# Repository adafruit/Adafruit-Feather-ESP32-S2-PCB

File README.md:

## Adafruit ESP32-S2 Feather

<a href="http://www.adafruit.com/products/5000"><br/>
Click here to purchase one from the Adafruit shop</a>

### ESP32-S2 Feather with BME280

<a href="http://www.adafruit.com/products/5303"><br/>
Click here to purchase one from the Adafruit shop</a>

PCB files for the Adafruit ESP32-S2 Feather 

Format is EagleCAD schematic and board layout
* https://www.adafruit.com/product/5000
* https://www.adafruit.com/product/5303

### Description

What's Feather-shaped and has an ESP32-S2 WiFi module? What has a STEMMA QT connector for I2C devices? What has your favorite Espressif WiFi microcontroller and lots of Flash and RAM memory for your next IoT project? What will make your next IoT project flyyyyy?

That's right - it's the new Adafruit ESP32-S2 Feather! With native USB and 4 MB flash + 2 MB of PSRAM, this board is perfect for use with CircuitPython or Arduino with low-cost WiFi. Native USB means it can act like a keyboard or a disk drive. WiFi means its awesome for IoT projects. And Feather means it works with the large community of Feather Wings for expandability.

The ESP32-S2 is a highly-integrated, low-power, 2.4 GHz Wi-Fi System-on-Chip (SoC) solution that now has built-in native USB as well as some other interesting new technologies like Time of Flight distance measurements. With its state-of-the-art power and RF performance, this SoC is an ideal choice for a wide variety of application scenarios relating to the Internet of Things (IoT), wearable electronics, and smart homes.

### License

Adafruit invests time and resources providing this open source design, please support Adafruit and open-source hardware by purchasing products from [Adafruit](https://www.adafruit.com)!

Designed by Limor Fried/Ladyada for Adafruit Industries.

Creative Commons Attribution/Share-Alike, all text above must be included in any redistribution. 
See license.txt for additional details.

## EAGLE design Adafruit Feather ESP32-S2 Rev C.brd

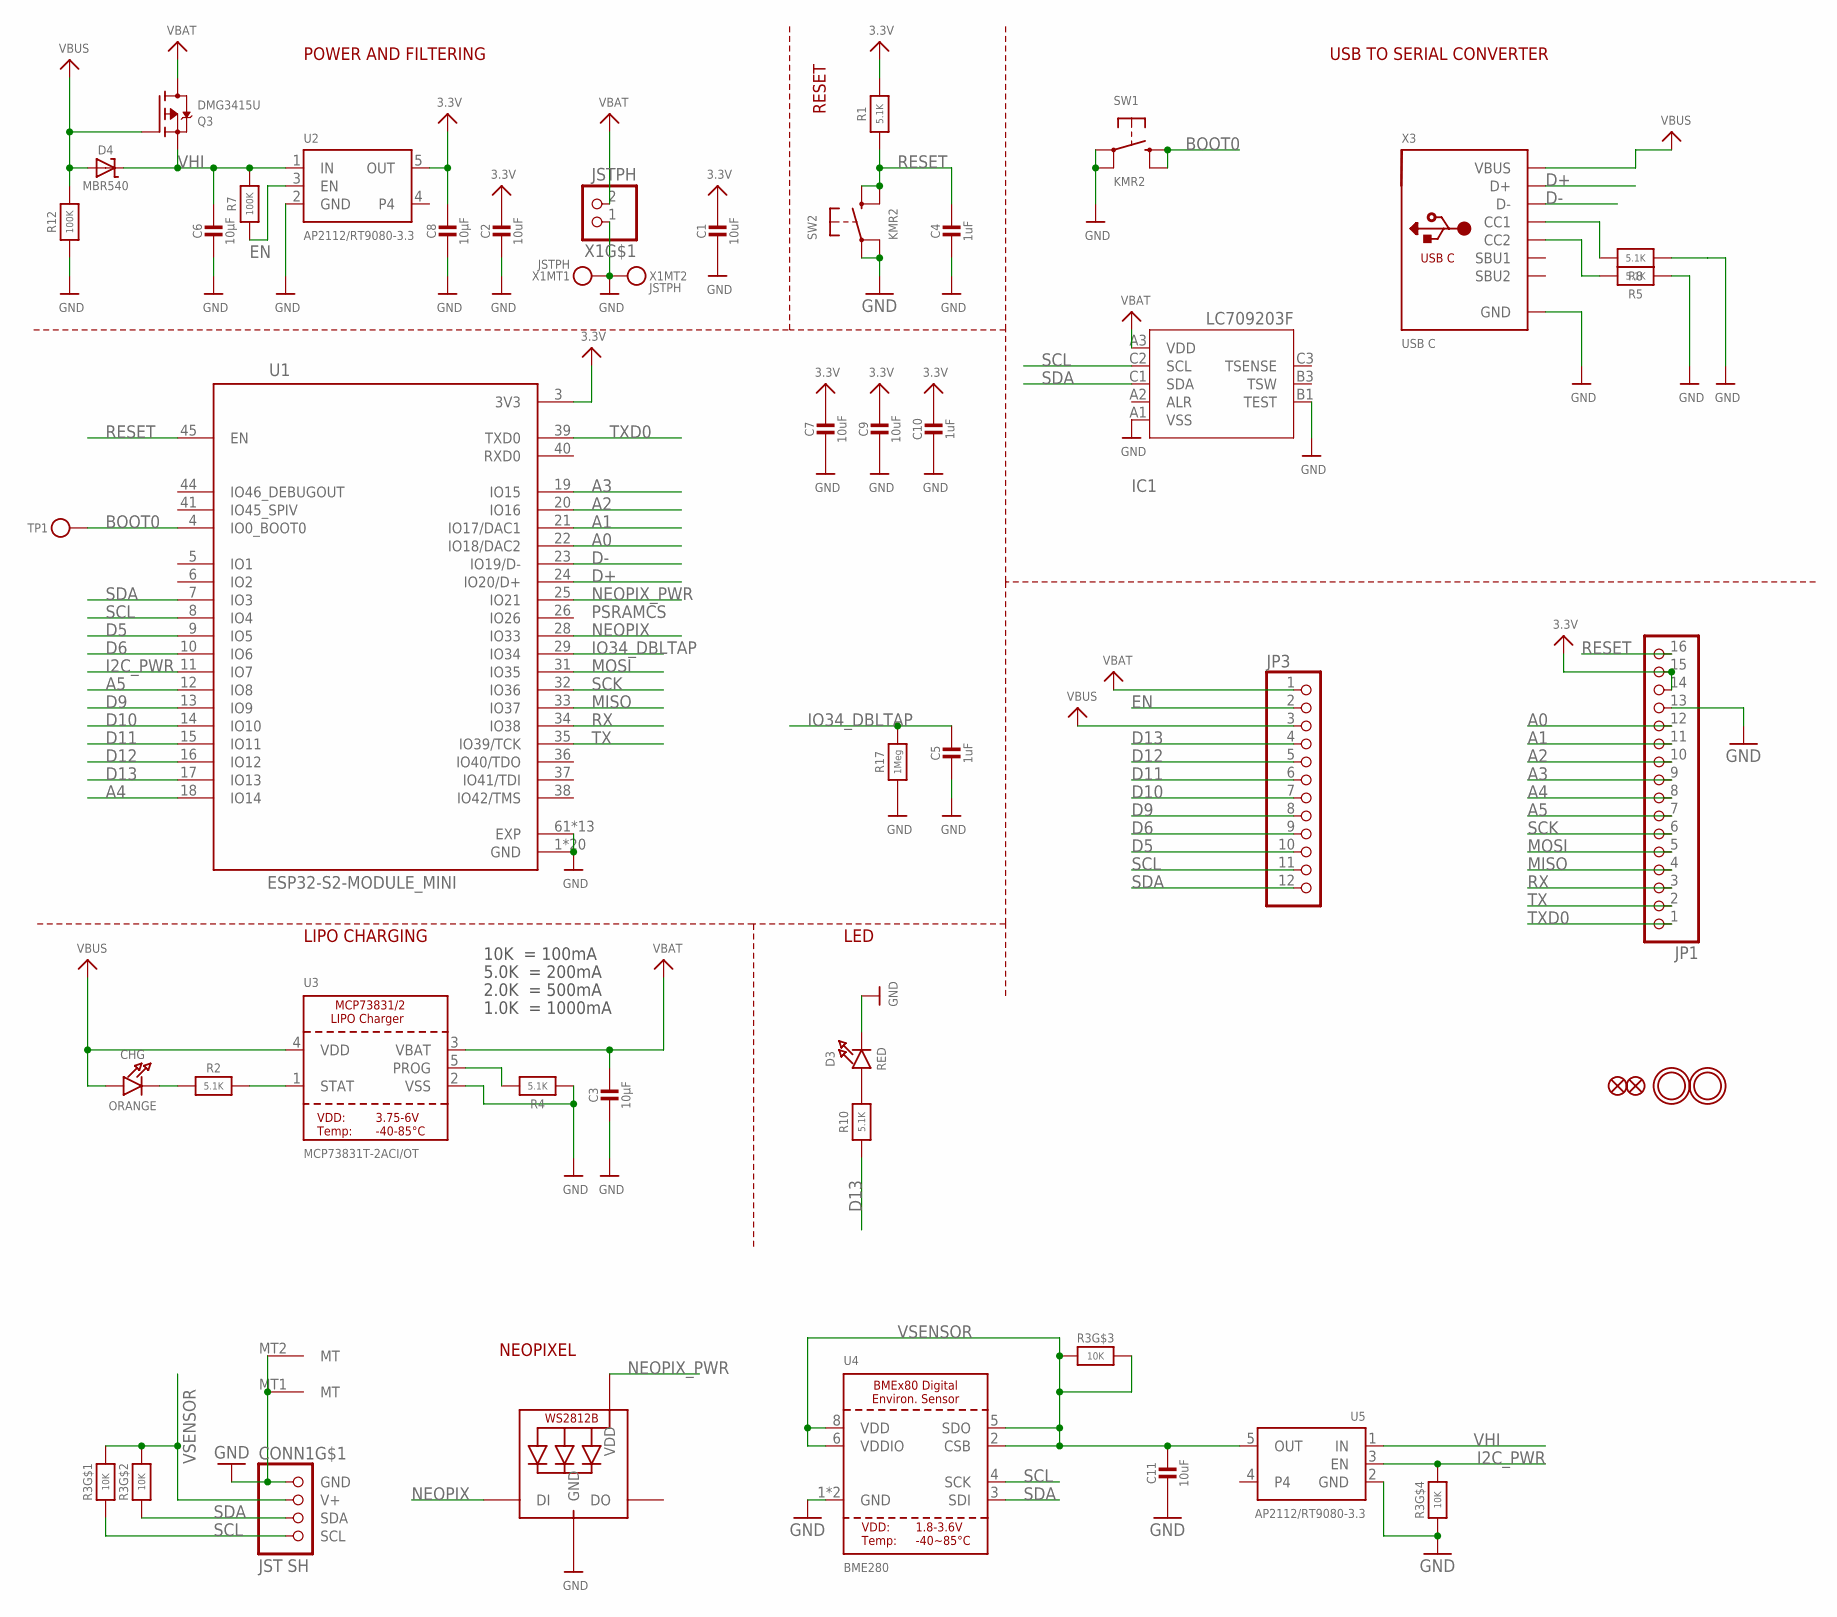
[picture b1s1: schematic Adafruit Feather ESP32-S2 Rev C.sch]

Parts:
C1, C2, C7, C9: 10uF; 0805-NO
C3, C6, C8: 10µF; 0805-NO
C4, C5, C10: 1uF; 0603-NO
C11: 10uF; _0805MP
CHG: ORANGE; CHIPLED_0603_NOOUTLINE
CONN1: JST SH; JST_SH4_RA
D3: RED; CHIPLED_0603_NOOUTLINE
D4: MBR540; SOD-123
IC1: LC709203F/MH; WLCSP9
JP1: HEADER-1X16ROUND; 1X16_ROUND
JP3: HEADER-1X12; 1X12_ROUND
LED1: WS2812B_SK6805_1515; SK6805_1515
Q3: DMG3415U; SOT23-R
R1, R2, R4, R5, R8, R10: 5.1K; 0603-NO
R3: 10K; RESPACK_4X0603
R7, R12: 100K; 0603-NO
R17: 1Meg; 0603-NO
SW1, SW2: KMR2; BTN_KMR2_4.6X2.8
TP1: TESTPOINTROUND1.5MMNO; TESTPOINT_ROUND_1.5MM_NO
U1: ESP32-S2-MODULE_MINI; QFN60_ESP32-S2-MINI-1_EXP
U2, U5: AP2112/RT9080-3.3; SOT23-5
U3: MCP73831T-2ACI/OT; SOT23-5
U4: BME280
U$31, U$32: MOUNTINGHOLE2.5; MOUNTINGHOLE_2.5_PLATED
U$34, U$35: FIDUCIAL_1MM
X1: JSTPH; JSTPH2_BATT
X3: USB C; USB_C_CUSB31-CFM2AX-01-X

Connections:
3.3V: C1.1, C2.1, C7.1, C8.1, C9.1, C10.1, JP1.14, JP1.15, R1.2, U1.3 (3V3), U2.5 (OUT)
A0: JP1.12, U1.22 (IO18/DAC2)
A1: JP1.11, U1.21 (IO17/DAC1)
A2: JP1.10, U1.20 (IO16)
A3: JP1.9, U1.19 (IO15)
A4: JP1.8, U1.18 (IO14)
A5: JP1.7, U1.12 (IO8)
BOOT0: SW1.B (S), SW1.B' (S1), TP1.P$1, U1.4 (IO0_BOOT0)
D5: JP3.10, U1.9 (IO5)
D6: JP3.9, U1.10 (IO6)
D9: JP3.8, U1.13 (IO9)
D10: JP3.7, U1.14 (IO10)
D11: JP3.6, U1.15 (IO11)
D12: JP3.5, U1.16 (IO12)
D13: JP3.4, R10.1, U1.17 (IO13)
D+: U1.24 (IO20/D+), X3.A6 (D+), X3.B6 (D+)
D-: U1.23 (IO19/D-), X3.A7 (D-), X3.B7 (D-)
EN: JP3.2, R7.1, U2.3 (EN)
GND: C1.2, C2.2, C3.2, C4.2, C5.2, C6.2, C7.2, C8.2, C9.2, C10.2, C11.2, CONN1.1 (GND), CONN1.MT1 (MT), CONN1.MT2 (MT), D3.C, IC1.A1 (VSS), IC1.B1 (TEST), JP1.13, LED1.4 (GND), R3.4 (1), R4.1, R5.1, R8.1, R12.1, R17.1, SW1.A, SW1.A' (P1), SW2.A, SW2.A' (P1), U1.1 (GND), U1.2 (GND), U1.30 (GND), U1.42 (GND), U1.43 (GND), U1.46 (GND), U1.47 (GND), U1.48 (GND), U1.49 (GND), U1.50 (GND), U1.51 (GND), U1.52 (GND), U1.53 (GND), U1.54 (GND), U1.55 (GND), U1.56 (GND), U1.57 (GND), U1.58 (GND), U1.59 (GND), U1.60 (GND), U1.61 (EXP), U1.62 (EXP), U1.63 (EXP), U1.64 (EXP), U1.65 (EXP), U1.66 (EXP), U1.67 (EXP), U1.68 (EXP), U1.69 (EXP), U1.70 (EXP), U1.71 (EXP), U1.72 (EXP), U1.73 (EXP), U2.2 (GND), U3.2 (VSS), U4.1 (GND), U4.7 (GND), U5.2 (GND), X1.1, X1.NC1, X1.NC2, X3.A1B12 (GND), X3.B1A12 (GND)
I2C_PWR: R3.5 (2), U1.11 (IO7), U5.3 (EN)
IO34_DBLTAP: C5.1, R17.2, U1.29 (IO34)
MISO: JP1.4, U1.33 (IO37)
MOSI: JP1.5, U1.31 (IO35)
unnamed: CHG.C, R2.1
unnamed: R2.2, U3.1 (STAT)
unnamed: R4.2, U3.5 (PROG)
unnamed: D3.A, R10.2
unnamed: R8.2, X3.A5 (CC1)
unnamed: R5.2, X3.B5 (CC2)
NEOPIX: LED1.1 (DI), U1.28 (IO33)
NEOPIX_PWR: LED1.2 (VDD), U1.25 (IO21)
RESET: C4.1, JP1.16, R1.1, SW2.B (S), SW2.B' (S1), U1.45 (EN)
RX: JP1.3, U1.34 (IO38)
SCK: JP1.6, U1.32 (IO36)
SCL: CONN1.4 (SCL), IC1.C2 (SCL), JP3.11, R3.1, U1.8 (IO4), U4.4 (SCK)
SDA: CONN1.3 (SDA), IC1.C1 (SDA), JP3.12, R3.2 (1), U1.7 (IO3), U4.3 (SDI)
TX: JP1.2, U1.35 (IO39/TCK)
TXD0: JP1.1, U1.39 (TXD0)
VBAT: C3.1, IC1.A3 (VDD), JP3.1, Q3.3 (D), U3.3 (VBAT), X1.2
VBUS: CHG.A, D4.A, JP3.3, Q3.1 (G), R12.2, U3.4 (VDD), X3.A4B9 (VBUS), X3.B4A9 (VBUS)
VHI: C6.1, D4.C, Q3.2 (S), R7.2, U2.1 (IN), U5.1 (IN)
VSENSOR: C11.1, CONN1.2 (V+), R3.3 (1), R3.6 (2), R3.7 (2), R3.8 (2), U4.2 (CSB), U4.5 (SDO), U4.6 (VDDIO), U4.8 (VDD), U5.5 (OUT)

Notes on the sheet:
POWER AND FILTERING
RESET
10K = 100mA
5.0K = 200mA
2.0K = 500mA
1.0K = 1000mA
USB TO SERIAL CONVERTER
LIPO CHARGING
LED
PSRAMCS
NEOPIXEL

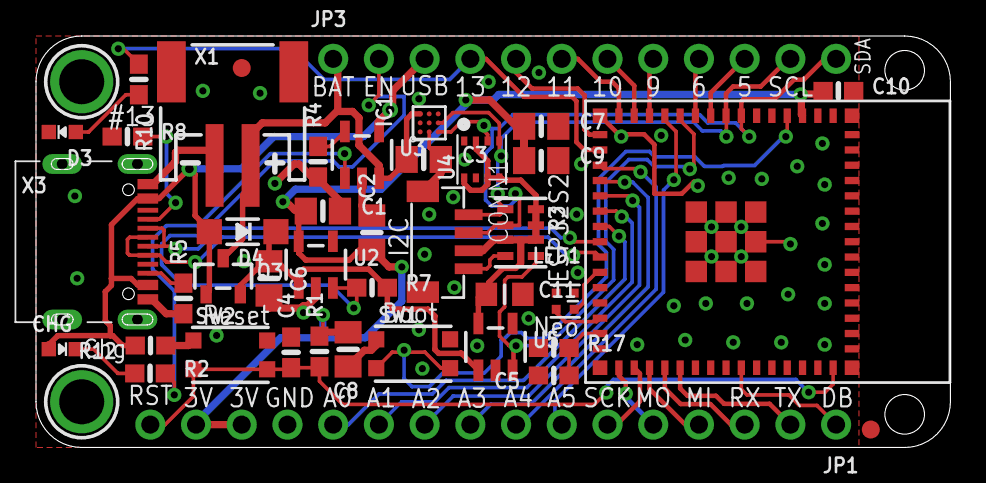
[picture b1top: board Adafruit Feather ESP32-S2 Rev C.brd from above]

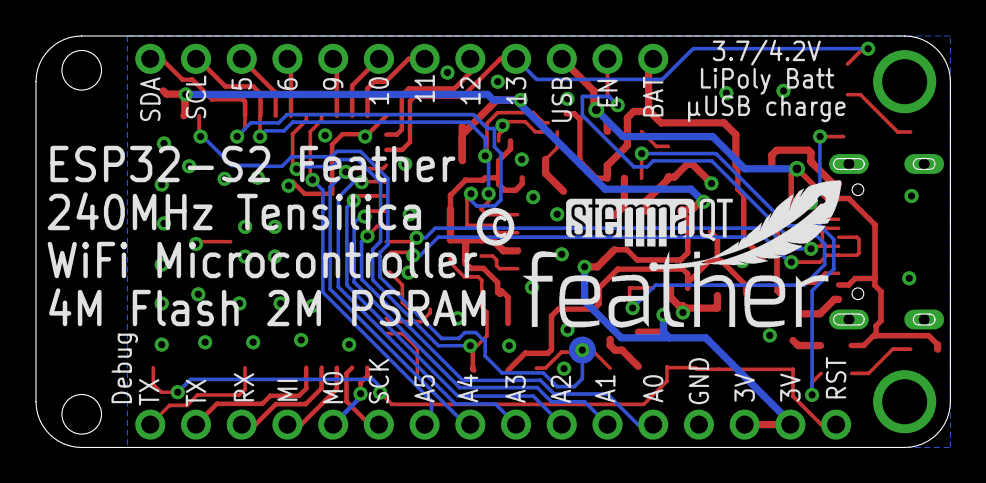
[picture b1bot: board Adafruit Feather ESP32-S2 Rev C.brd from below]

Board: 2 copper layers, 50.8 x 22.9 mm, 47 parts (4 on the bottom side), 42 nets.

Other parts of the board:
U$14: PCBFEAT-REV-040
U$15: FEATHERLOGO_MED
U$53: STEMMAQT

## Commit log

2021-11-22 Renamed files
2021-11-29 Add PrettyPins
2021-11-29 Add PrettyPins.
2021-12-03 Add factory reset file.
2021-12-23 add i2c scan
2022-01-04 Update file name.
2022-03-21 Update PrettyPins.
2022-03-21 Add rev C board files.
2023-06-21 Updating factory reset files
    Updating factory reset files to check for either LC or MAX battery monitors

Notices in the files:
parts and their libraries:
microbuilder: This work is placed in the public domain, and may be freely used for commercial and non-commercial work with the following conditions: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
